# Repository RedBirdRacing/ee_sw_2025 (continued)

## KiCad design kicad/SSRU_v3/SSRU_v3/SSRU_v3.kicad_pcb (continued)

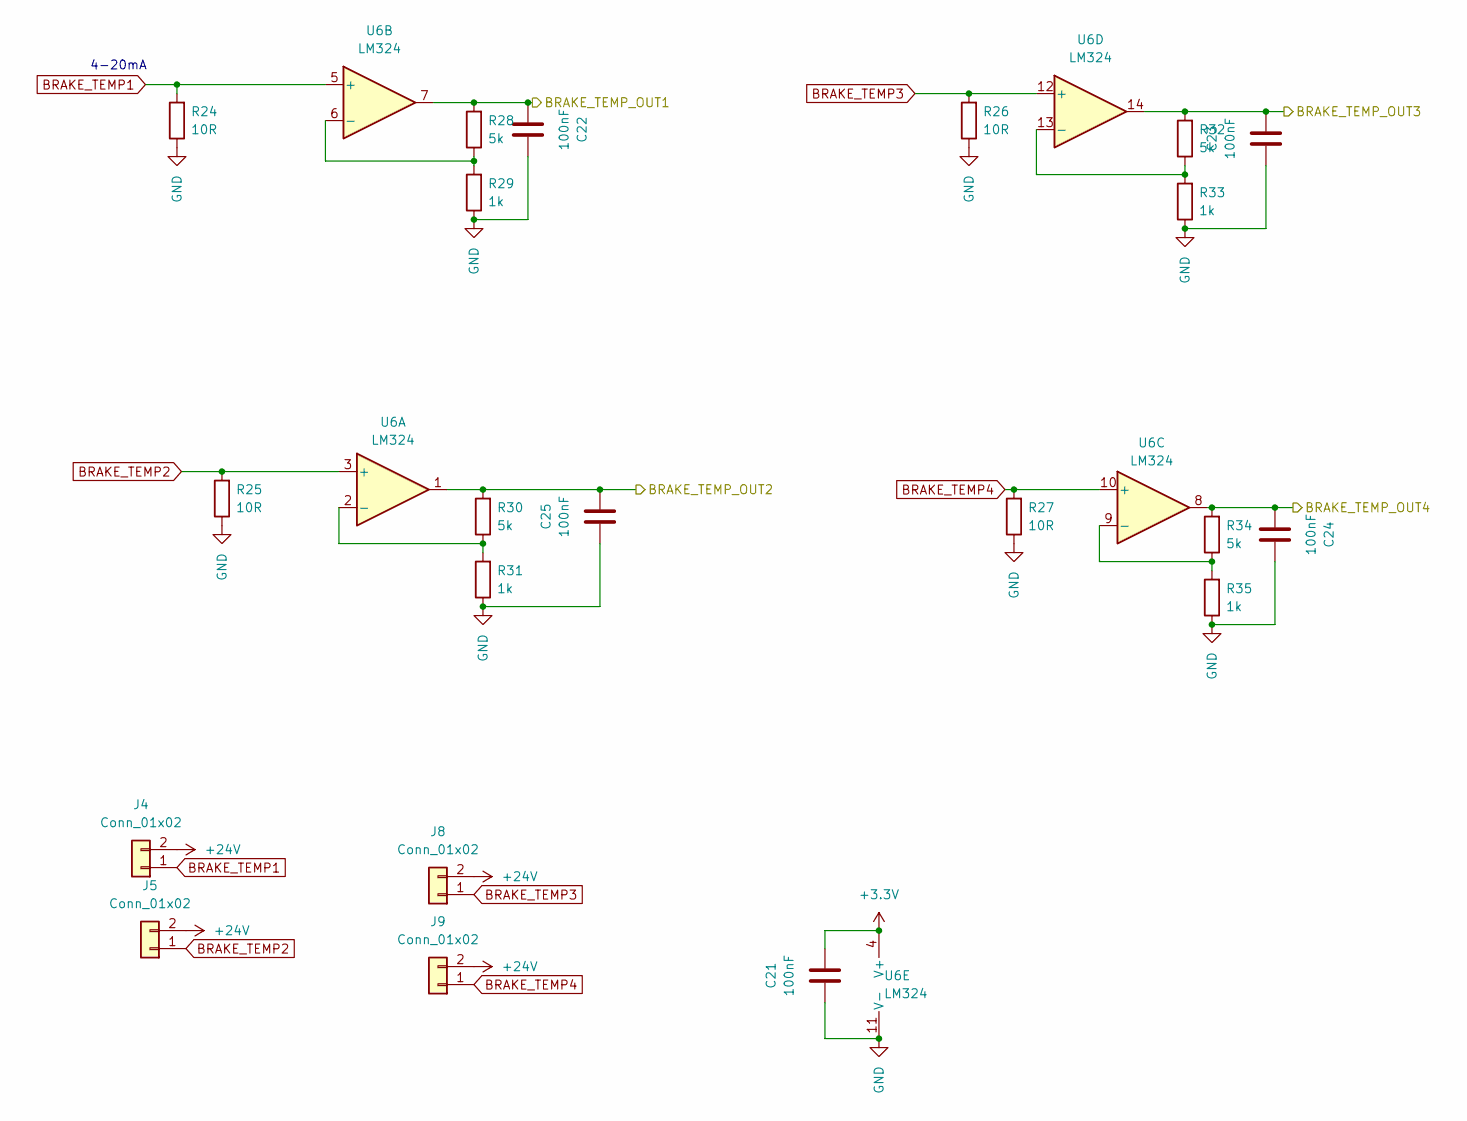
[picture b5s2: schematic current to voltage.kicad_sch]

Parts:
C21, C22, C23, C24, C25: 100nF; C_0805_2012Metric_Pad1.18x1.45mm_HandSolder_L
J4, J5, J8, J9: Conn_01x02; JST_XH_B2B-XH-A_1x02_P2.50mm_Vertical
R24, R25, R26, R27: 10R; R_1206_3216Metric_Pad1.30x1.75mm_HandSolder_RMC
R28, R30, R32, R34: 5k; R_0805_2012Metric_Pad1.20x1.40mm_HandSolder_L
R29, R31, R33, R35: 1k; R_0805_2012Metric_Pad1.20x1.40mm_HandSolder_L
U6: LM324; SOIC127P600X175-14N

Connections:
+3.3V: C21.1, U6.4 (V+); also elsewhere on the board
+24V: J4.2, J5.2, J8.2, J9.2; also elsewhere on the board
BRAKE_TEMP1: J4.1, R24.2, U6.5 (+)
BRAKE_TEMP2: J5.1, R25.2, U6.3 (+)
BRAKE_TEMP3: J8.1, R26.2, U6.12 (+)
BRAKE_TEMP4: J9.1, R27.2, U6.10 (+)
BRAKE_TEMP_OUT1: C22.1, R28.2, U6.7; also elsewhere on the board
BRAKE_TEMP_OUT2: C25.1, R30.2, U6.1; also elsewhere on the board
BRAKE_TEMP_OUT3: C23.1, R32.2, U6.14; also elsewhere on the board
BRAKE_TEMP_OUT4: C24.1, R34.2, U6.8; also elsewhere on the board
GND: C21.2, C22.2, C23.2, C24.2, C25.2, R24.1, R25.1, R26.1, R27.1, R29.1, R31.1, R33.1, R35.1, U6.11 (V-); also elsewhere on the board
unnamed: R30.1, R31.2, U6.2 (-)
unnamed: R28.1, R29.2, U6.6 (-)
unnamed: R34.1, R35.2, U6.9 (-)
unnamed: R32.1, R33.2, U6.13 (-)

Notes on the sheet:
4-20mA

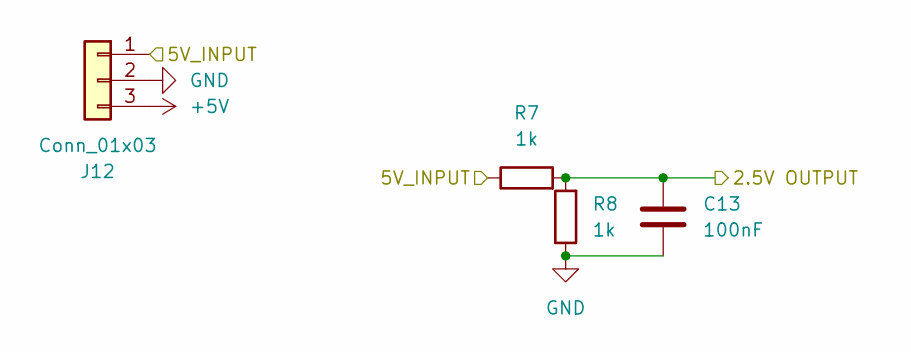
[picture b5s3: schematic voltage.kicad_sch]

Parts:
C13: 100nF; C_0805_2012Metric_Pad1.18x1.45mm_HandSolder_L
J12: Conn_01x03; JST_XH_B3B-XH-A_1x03_P2.50mm_Vertical
R7, R8: 1k; R_0805_2012Metric_Pad1.20x1.40mm_HandSolder_L

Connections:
+5V: J12.3; also elsewhere on the board
GND: C13.1, J12.2, R8.1; also elsewhere on the board
POT1_IN: J12.1, R7.1
POT1_OUT: C13.2, R7.2, R8.2; also elsewhere on the board

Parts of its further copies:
C14, C15, C16: 100nF; C_0805_2012Metric_Pad1.18x1.45mm_HandSolder_L
J13, J14, J15: Conn_01x03; JST_XH_B3B-XH-A_1x03_P2.50mm_Vertical
R9, R10, R11, R12, R13, R14: 1k; R_0805_2012Metric_Pad1.20x1.40mm_HandSolder_L

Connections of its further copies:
+5V: J13.3, J14.3, J15.3; also elsewhere on the board
GND: C14.1, C15.1, C16.1, J13.2, J14.2, J15.2, R10.1, R12.1, R14.1; also elsewhere on the board
POT2_IN: J13.1, R9.1
POT2_OUT: C14.2, R9.2, R10.2; also elsewhere on the board
POT3_IN: J15.1, R13.1
POT3_OUT: C16.2, R13.2, R14.2; also elsewhere on the board
POT4_IN: J14.1, R11.1
POT4_OUT: C15.2, R11.2, R12.2; also elsewhere on the board

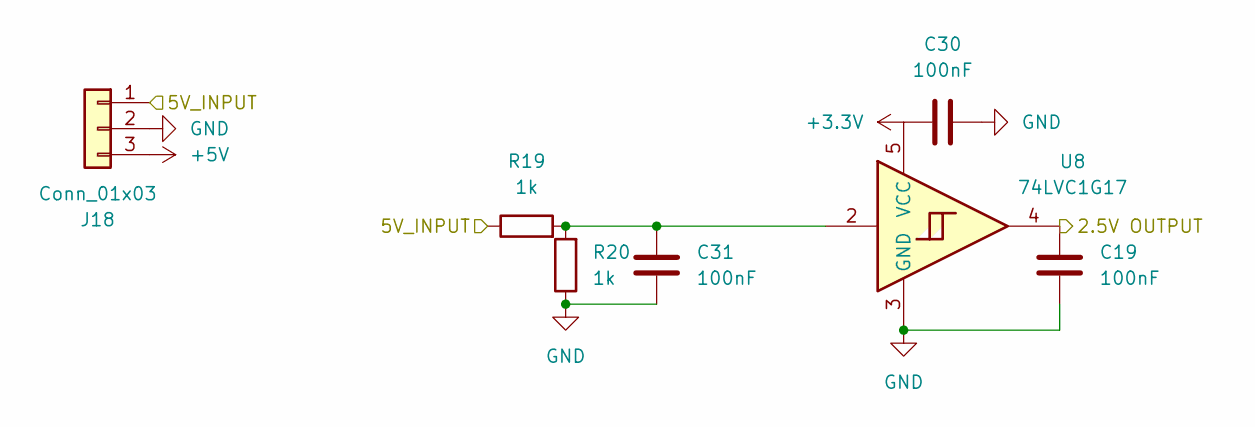
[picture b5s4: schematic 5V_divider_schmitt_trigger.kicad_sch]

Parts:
C19, C30, C31: 100nF; C_0805_2012Metric_Pad1.18x1.45mm_HandSolder_L
J18: Conn_01x03; JST_XH_B3B-XH-A_1x03_P2.50mm_Vertical
R19, R20: 1k; R_0805_2012Metric_Pad1.20x1.40mm_HandSolder_L
U8: 74LVC1G17; SOT-23-5_HandSoldering

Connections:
+3.3V: C30.2, U8.5 (VCC); also elsewhere on the board
+5V: J18.3; also elsewhere on the board
FLOW_IN: J18.1, R19.1
FLOW_OUT: C19.2, U8.4; also elsewhere on the board
GND: C19.1, C30.1, C31.1, J18.2, R20.1, U8.3 (GND); also elsewhere on the board
unnamed: C31.2, R19.2, R20.2, U8.2

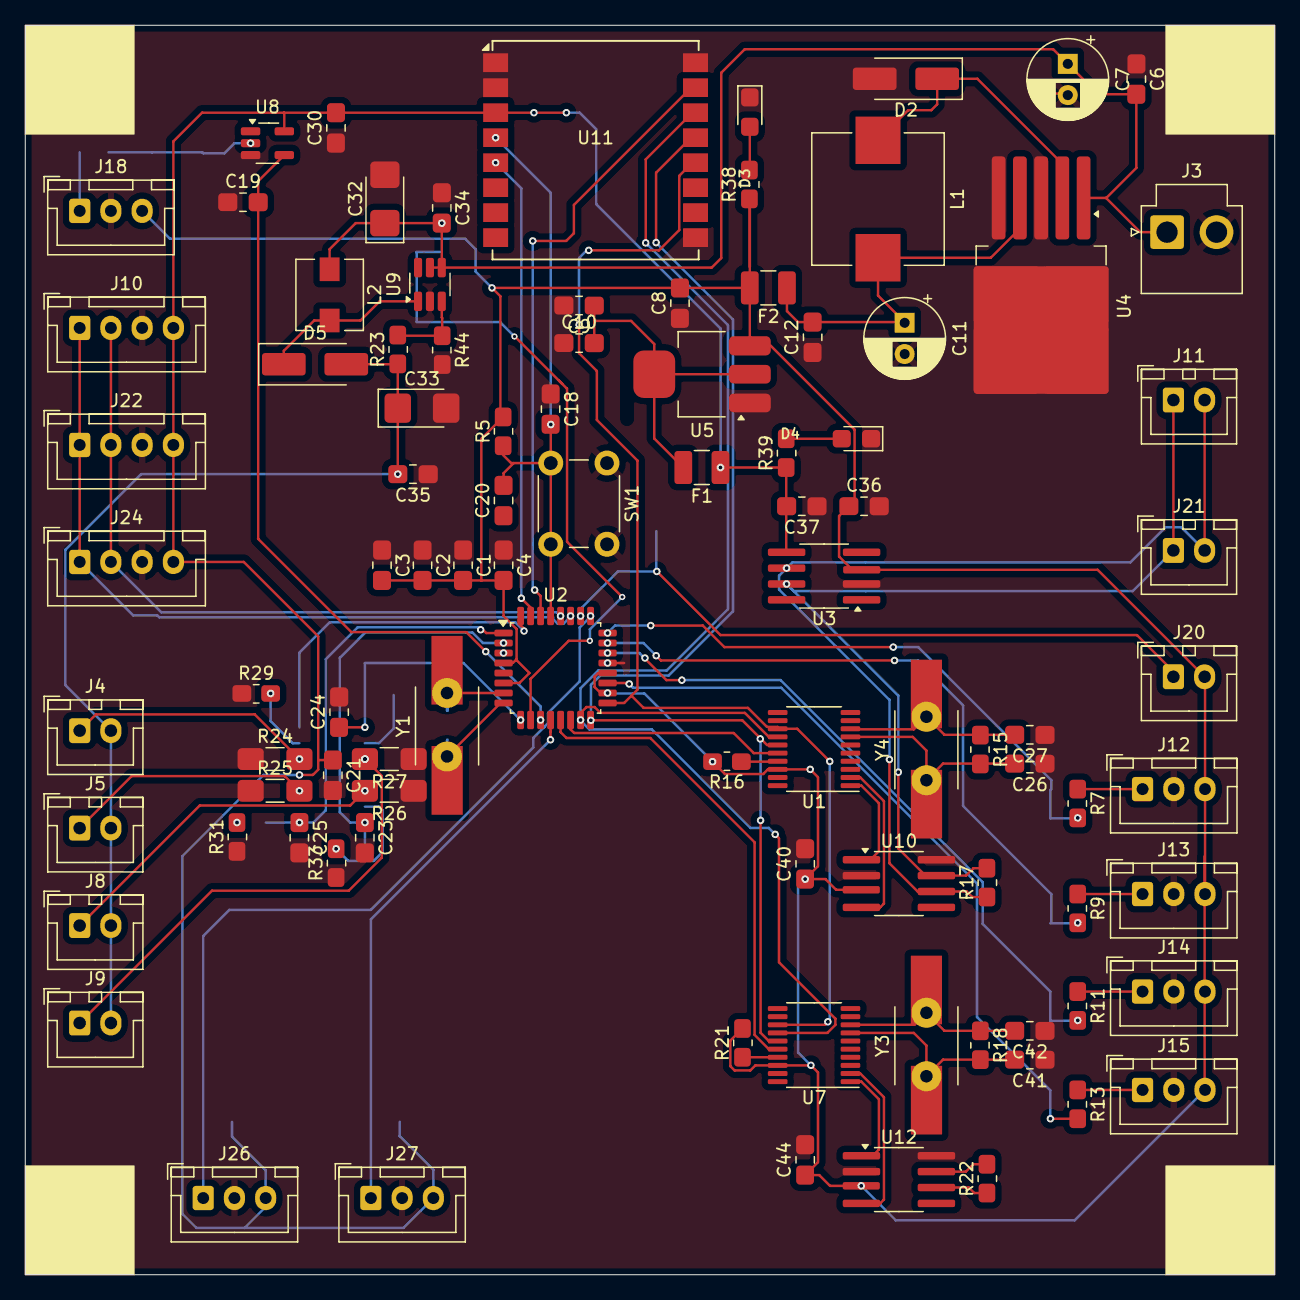
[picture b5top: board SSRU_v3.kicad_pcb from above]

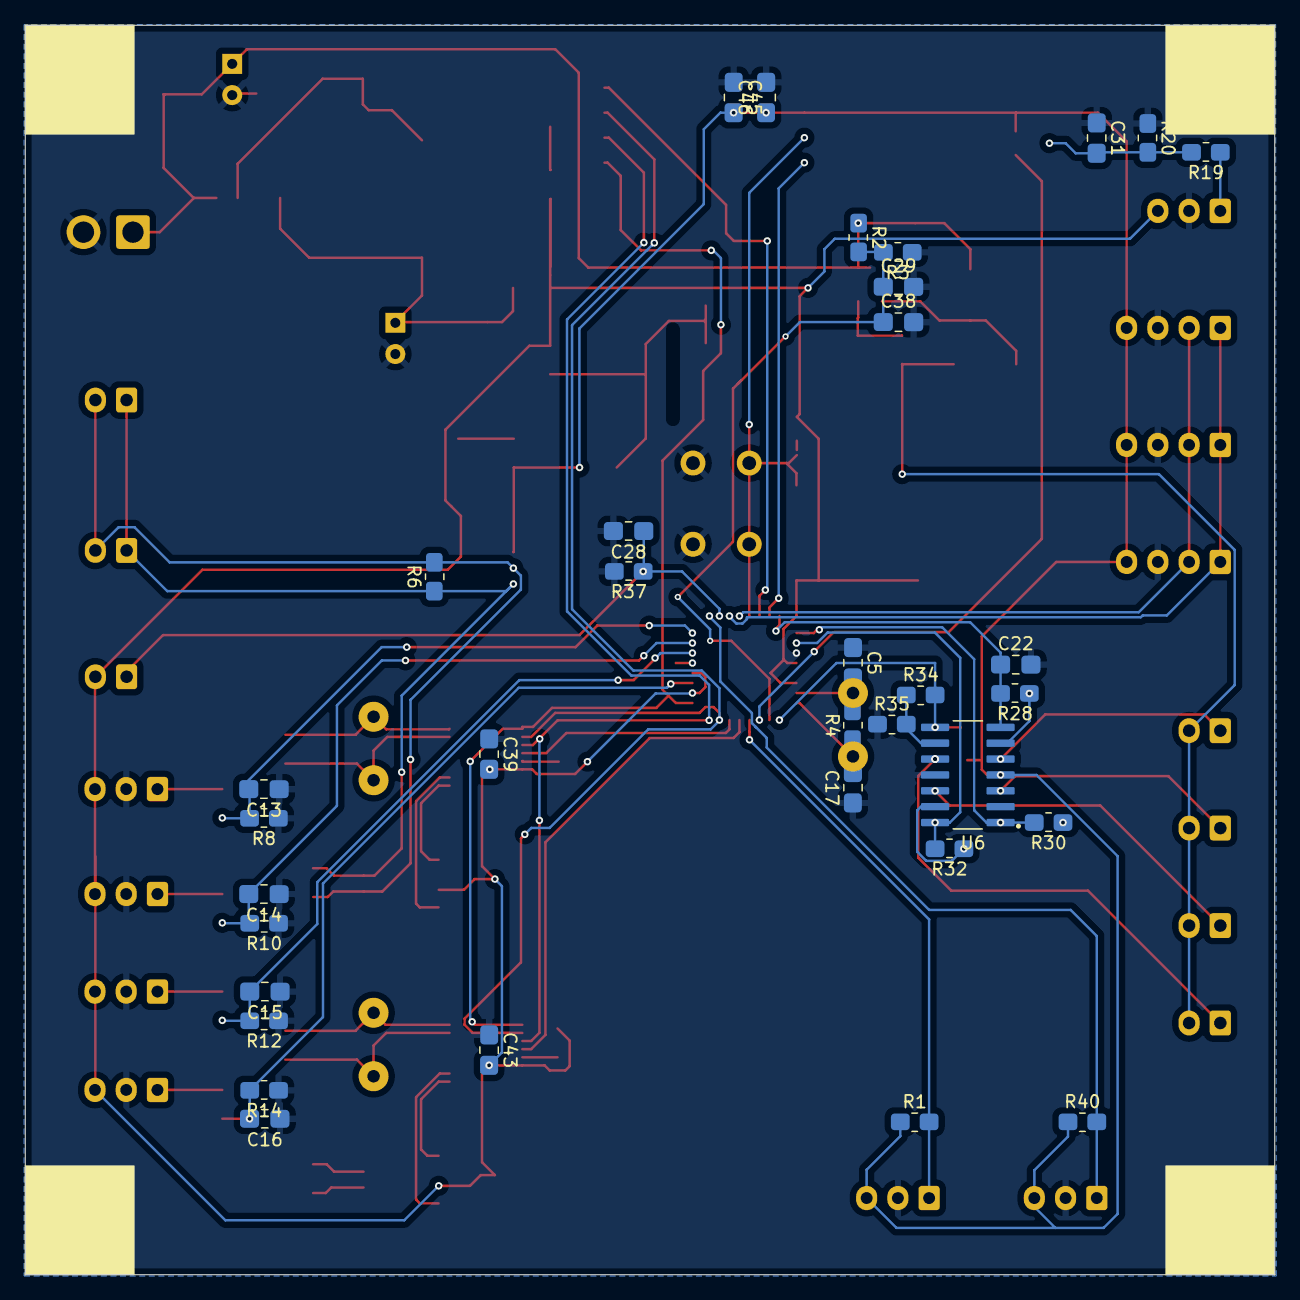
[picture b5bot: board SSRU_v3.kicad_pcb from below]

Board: 2 copper layers, 100.0 x 100.0 mm, 132 parts (34 on the bottom side), 63 nets.

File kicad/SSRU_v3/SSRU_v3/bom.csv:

"Reference","Value","Datasheet","Footprint","Qty","DNP"
"C1,C3,C4,C5,C6,C8,C10,C12,C13,C14,C15,C16,C17,C18,C19,C20,C21,C22,C23,C24,C25,C26,C27,C28,C29,C30,C31,C34,C35,C36,C37,C38","100nF","~","RMC_Capacitor:C_0805_2012Metric_Pad1.18x1.45mm_HandSolder_L","32",""
"C2","10uF","~","RMC_Capacitor:C_0805_2012Metric_Pad1.18x1.45mm_HandSolder_L","1",""
"C7","100uF","~","Capacitor_THT:CP_Radial_D6.3mm_P2.50mm","1",""
"C9,C32,C33","22uF","~","-- mixed values --","3",""
"C11","330uF","~","Capacitor_THT:CP_Radial_D6.3mm_P2.50mm","1",""
"D1","D","~","Diode_SMD:D_SMA_Handsoldering","1",""
"D2,D5","SMA Diode","~","Diode_SMD:D_SMA_Handsoldering","2",""
"D3,D4","LED","~","RMC_LED:LED_0805_2012Metric_Pad1.45x1.40mm_HandSolder","2",""
"F1,F2","Fuse","~","Fuse:Fuse_1210_3225Metric_Pad1.42x2.65mm_HandSolder","2",""
"J1,J12,J13,J14,J15,J16,J17,J18,J19,J23,J26,J27","Conn_01x03","~","Connector_JST:JST_XH_B3B-XH-A_1x03_P2.50mm_Vertical","12",""
"J2","USB_C_Receptacle_USB2.0_14P","https://www.usb.org/sites/default/files/documents/usb_type-c.zip","RMC_Connnector:USB_C_Receptacle_G-Switch_GT-USB-7010ASV_Handsolder","1",""
"J3,J4,J5,J8,J9,J11,J20,J21","Conn_01x02","~","-- mixed values --","8",""
"J6,J7,J10,J25","Conn_01x04","~","Connector_JST:JST_XH_B4B-XH-A_1x04_P2.50mm_Vertical","4",""
"L1","330uH","~","RMC_Inductor:L_10.4x10.4_H4.8","1",""
"L2","4.7-22uH","~","Inductor_SMD:L_Wuerth_HCI-5040","1",""
"Q1,Q2","MMBT3904","https://www.onsemi.com/pdf/datasheet/pzt3904-d.pdf","Package_TO_SOT_SMD:SOT-23_Handsoldering","2",""
"R1,R36,R40","4k7","~","RMC_Resistor:R_0805_2012Metric_Pad1.20x1.40mm_HandSolder_L","3",""
"R2,R7,R8,R9,R10,R11,R12,R13,R14,R15,R16,R17,R18,R19,R20,R21,R22,R29,R31,R33,R35","1k","~","RMC_Resistor:R_0805_2012Metric_Pad1.20x1.40mm_HandSolder_L","21",""
"R3,R28,R30,R32,R34","5k","~","RMC_Resistor:R_0805_2012Metric_Pad1.20x1.40mm_HandSolder_L","5",""
"R4,R5","10K","~","RMC_Resistor:R_0805_2012Metric_Pad1.20x1.40mm_HandSolder_L","2",""
"R6,R39","120R","~","RMC_Resistor:R_0805_2012Metric_Pad1.20x1.40mm_HandSolder_L","2",""
"R23","249k","~","RMC_Resistor:R_0805_2012Metric_Pad1.20x1.40mm_HandSolder_L","1",""
"R24,R25,R26,R27","10R","~","RMC_Resistor:R_1206_3216Metric_Pad1.30x1.75mm_HandSolder_RMC","4",""
"R37","100K","~","RMC_Resistor:R_0805_2012Metric_Pad1.20x1.40mm_HandSolder_L","1",""
"R38","330R","~","RMC_Resistor:R_0805_2012Metric_Pad1.20x1.40mm_HandSolder_L","1",""
"R41,R42","5k1","~","RMC_Resistor:R_0805_2012Metric_Pad1.20x1.40mm_HandSolder_L","2",""
"R43","499R","~","RMC_Resistor:R_0805_2012Metric_Pad1.20x1.40mm_HandSolder_L","1",""
"R44","680R","~","RMC_Resistor:R_0805_2012Metric_Pad1.20x1.40mm_HandSolder_L","1",""
"SW1,SW2","SW_SPST","~","Button_Switch_THT:SW_PUSH_6mm_H5mm","2",""
"U1","ESP32-S3-WROOM-2","https://www.espressif.com/sites/default/files/documentation/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","to be sorted:ESP32-WROOM-S3-2","1",""
"U2","CH340C","https://datasheet.lcsc.com/szlcsc/Jiangsu-Qin-Heng-CH340C_C8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","RMC_SO:SOIC-16_3.9x9.9mm_P1.27mm_Handsolder","1",""
"U3","TJA1051T-3","http://www.nxp.com/docs/en/data-sheet/TJA1051.pdf","RMC_SO:SOIC-8_3.9x4.9mm_P1.27mm_RMC_Handsolder","1",""
"U4","LM2576S-5","http://www.ti.com/lit/ds/symlink/lm2576.pdf","RMC_TO:TO-263-5_TabPin3_Handsolder","1",""
"U5","AMS1117-3.3","http://www.advanced-monolithic.com/pdf/ds1117.pdf","RMC_SOT:SOT-223-3_TabPin2_Handsolder","1",""
"U6","LM324","http://www.ti.com/lit/ds/symlink/lm2902-n.pdf","RMC_SO:SOIC127P600X175-14N","1",""
"U7","TXS0102DCU","http://www.ti.com/lit/gpn/txs0102","Package_SO:VSSOP-8_2.3x2mm_P0.5mm","1",""
"U8","74LVC1G17","https://www.ti.com/lit/ds/symlink/sn74lvc1g17.pdf","Package_TO_SOT_SMD:SOT-23-5_HandSoldering","1",""
"U9","MT3608/SDB628","https://www.olimex.com/Products/Breadboarding/BB-PWR-3608/re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","Package_TO_SOT_SMD:SOT-23-6_Handsoldering","1",""

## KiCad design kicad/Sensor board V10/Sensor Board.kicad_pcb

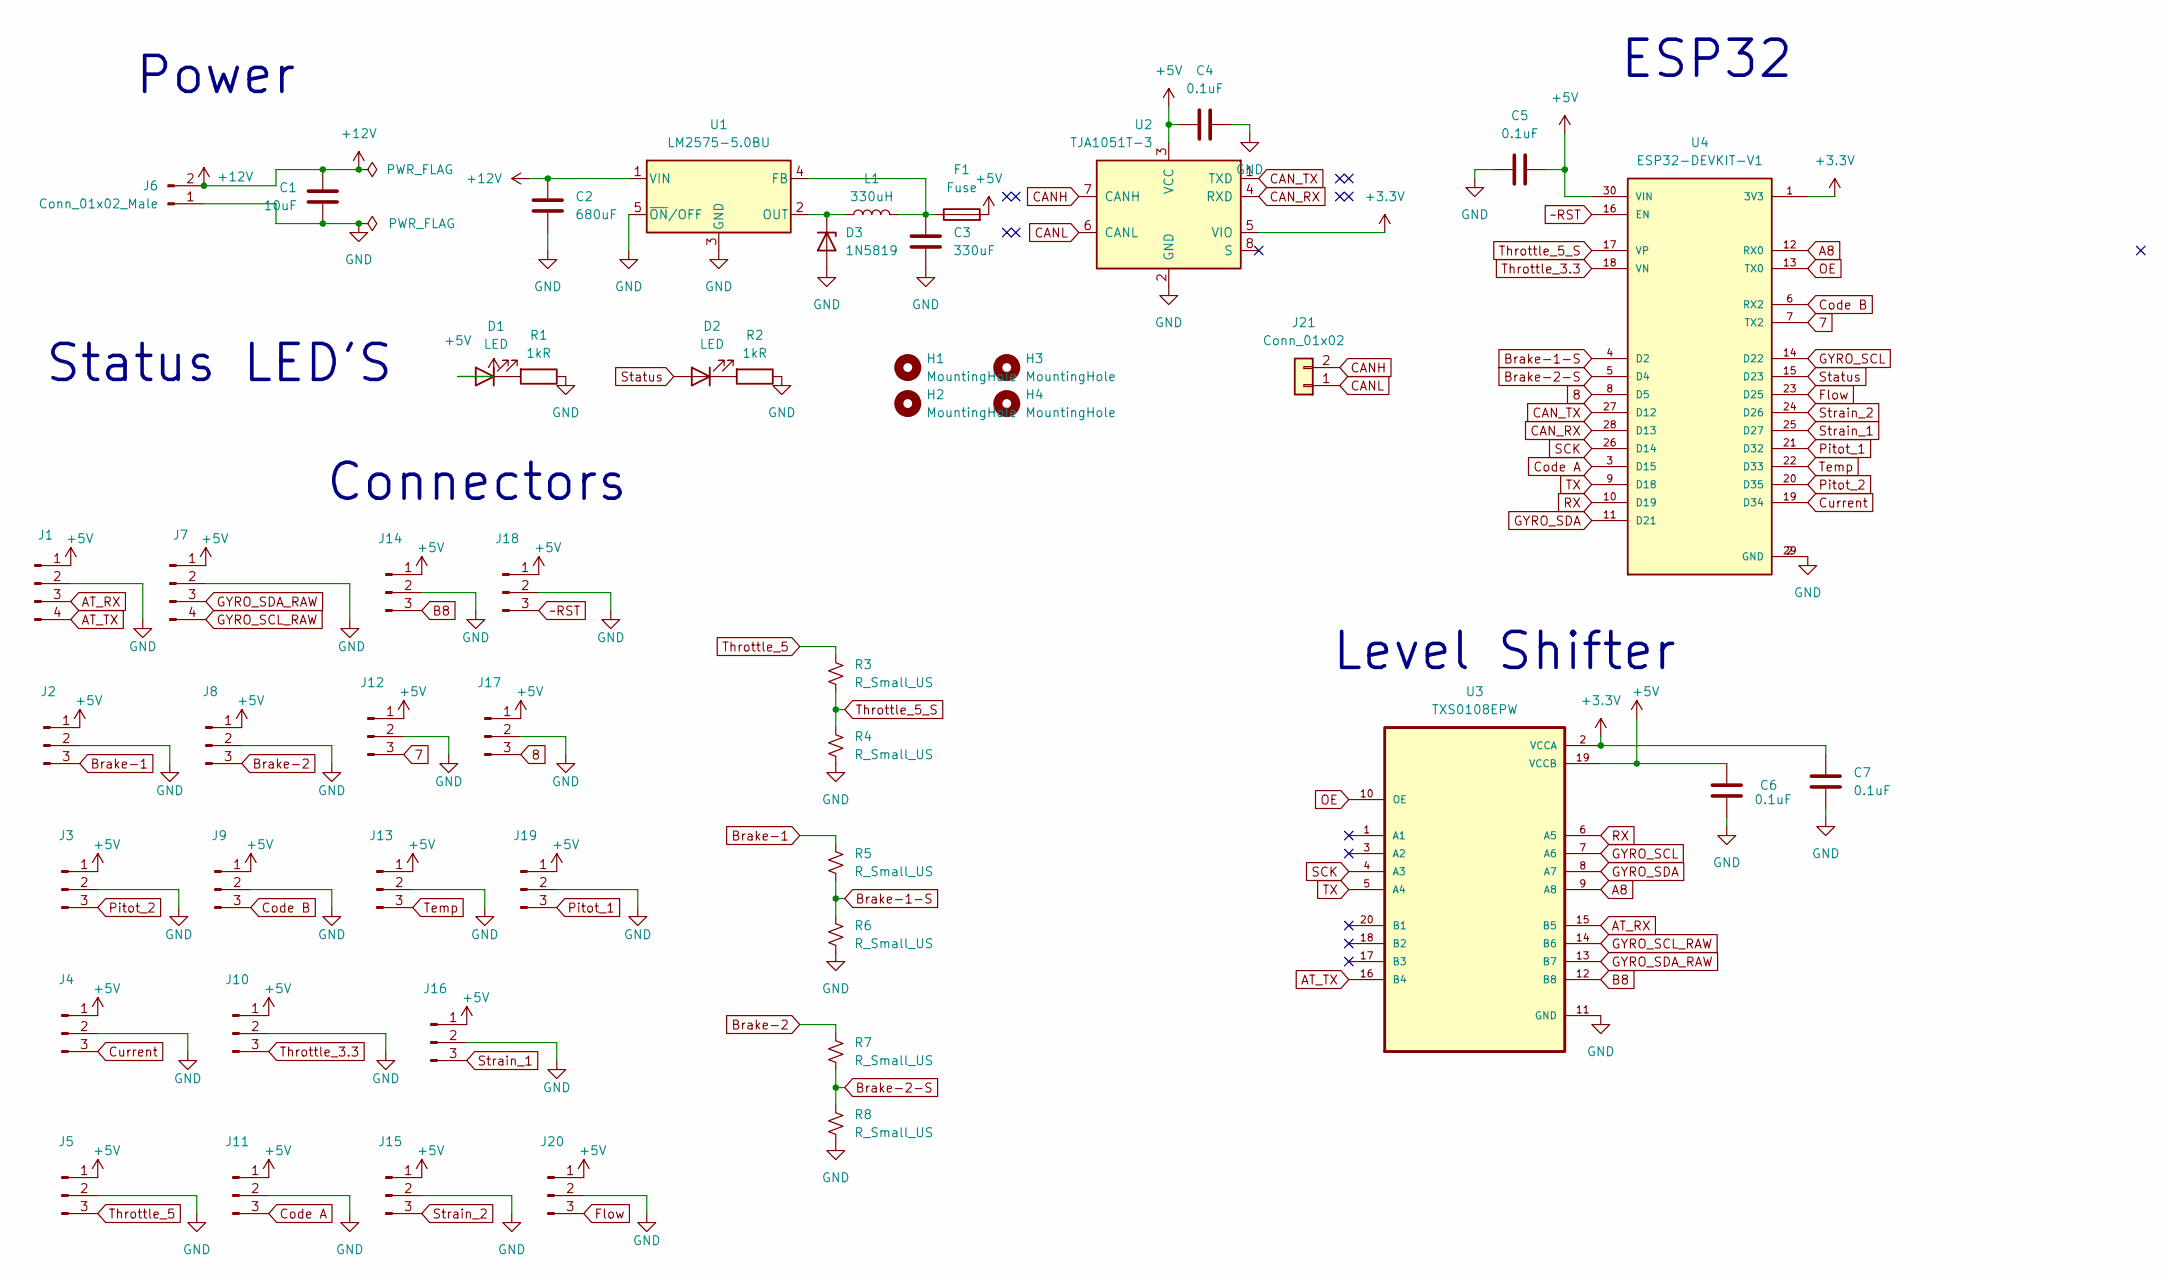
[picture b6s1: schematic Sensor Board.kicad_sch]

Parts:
C1: 10uF; C_0805_2012Metric_Pad1.18x1.45mm_HandSolder_L
C2: 680uF; CP_Radial_D10.0mm_P5.00mm_F
C3: 330uF; CP_Radial_D10.0mm_P5.00mm_F
C4, C5, C6, C7: 0.1uF; C_0805_2012Metric_Pad1.18x1.45mm_HandSolder_L
D1, D2: LED; LED_0805_2012Metric_Pad1.45x1.40mm_HandSolder
D3: 1N5819; D_SMA_Handsoldering
F1: Fuse; Fuse_1210_3225Metric_Pad1.42x2.65mm_HandSolder
H1, H2, H3, H4: MountingHole; MountingHole_3.2mm_M3
J1, J7: Conn_01x04_Pin; JST_XH_B4B-XH-A_1x04_P2.50mm_Vertical
J2, J3, J4, J5, J8, J9, J10, J11, J12, J13, J14, J15, J16, J17, J18, J19, J20: Conn_01x03_Pin; JST_XH_B3B-XH-A_1x03_P2.50mm_Vertical
J6: Conn_01x02_Male; JST_VH_B2P-VH_1x02_P3.96mm_Vertical
J21: Conn_01x02; JST_XH_B2B-XH-A_1x02_P2.50mm_Vertical
L1: 330uH; L_10.4x10.4_H4.8
R1, R2: 1kR; R_0805_2012Metric_Pad1.20x1.40mm_HandSolder_L
R3, R4, R5, R6, R7, R8: R_Small_US; R_0805_2012Metric_Pad1.20x1.40mm_HandSolder_L
U1: LM2575-5.0BU; TO-263-5_TabPin3
U2: TJA1051T-3; SOIC-8_3.9x4.9mm_P1.27mm
U3: TXS0108EPW; TSSOP-20_4.4x6.5mm_P0.65mm
U4: ESP32-DEVKIT-V1; MODULE_ESP32_DEVKIT_V1; PARTREV N/A

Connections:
7: J12.3, U4.7 (TX2)
8: J17.3, U4.8 (D5)
+3.3V: C7.2, U2.5 (VIO), U3.2 (VCCA), U4.1 (3V3)
+5V: C4.1, C5.1, C6.2, D1.2 (A), F1.2, J1.1, J2.1, J3.1, J4.1, J5.1, J7.1, J8.1, J9.1, J10.1, J11.1, J12.1, J13.1, J14.1, J15.1, J16.1, J17.1, J18.1, J19.1, J20.1, U2.3 (VCC), U3.19 (VCCB), U4.30 (VIN)
+12V: C1.1, C2.1, J6.2, U1.1 (VIN)
A8: U3.9 (A8), U4.12 (RX0)
AT_RX: J1.3, U3.15 (B5)
AT_TX: J1.4, U3.16 (B4)
B8: J14.3, U3.12 (B8)
Brake-1: J2.3, R5.1
Brake-1-S: R5.2, R6.1, U4.4 (D2)
Brake-2: J8.3, R7.1
Brake-2-S: R7.2, R8.1, U4.5 (D4)
CANH: J21.2, U2.7 (CANH)
CANL: J21.1, U2.6 (CANL)
CAN_RX: U2.4 (RXD), U4.28 (D13)
CAN_TX: U2.1 (TXD), U4.27 (D12)
Code A: J11.3, U4.3 (D15)
Code B: J9.3, U4.6 (RX2)
Current: J4.3, U4.19 (D34)
Flow: J20.3, U4.23 (D25)
GND: C1.2, C2.2, C3.2, C4.2, C5.2, C6.1, C7.1, D3.2 (A), J1.2, J2.2, J3.2, J4.2, J5.2, J6.1, J7.2, J8.2, J9.2, J10.2, J11.2, J12.2, J13.2, J14.2, J15.2, J16.2, J17.2, J18.2, J19.2, J20.2, R1.1, R2.1, R4.2, R6.2, R8.2, U1.3 (GND), U1.5 (~ON/OFF), U2.2 (GND), U3.11 (GND), U4.2 (GND), U4.29 (GND)
GYRO_SCL: U3.7 (A6), U4.14 (D22)
GYRO_SCL_RAW: J7.4, U3.14 (B6)
GYRO_SDA: U3.8 (A7), U4.11 (D21)
GYRO_SDA_RAW: J7.3, U3.13 (B7)
unnamed: D1.1 (K), R1.2
unnamed: D2.1 (K), R2.2
unnamed: D3.1 (K), L1.1, U1.2 (OUT)
unnamed: C3.1, F1.1, L1.2, U1.4 (FB)
OE: U3.10 (OE), U4.13 (TX0)
Pitot_1: J19.3, U4.21 (D32)
Pitot_2: J3.3, U4.20 (D35)
RX: U3.6 (A5), U4.10 (D19)
SCK: U3.4 (A3), U4.26 (D14)
Status: D2.2 (A), U4.15 (D23)
Strain_1: J16.3, U4.25 (D27)
Strain_2: J15.3, U4.24 (D26)
TX: U3.5 (A4), U4.9 (D18)
Temp: J13.3, U4.22 (D33)
Throttle_3.3: J10.3, U4.18 (VN)
Throttle_5: J5.3, R3.1
Throttle_5_S: R3.2, R4.1, U4.17 (VP)
~RST: J18.3, U4.16 (EN)

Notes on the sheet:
Status LED'S
Power
Connectors
ESP32
Level Shifter

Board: 2 copper layers, 49 parts (9 on the bottom side), 44 nets, no tracks yet.
